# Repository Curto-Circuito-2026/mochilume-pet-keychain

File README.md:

# 🎮 Mochilume: Portable Wireless Battle Console & OS

O **Mochilume** é um console portátil de bolso open-hardware projetado para trazer de volta a nostalgia dos bichinhos virtuais (estilo Tamagotchi), combinando mecânicas de exploração do mundo real (estilo Pokémon GO) com batalhas multijogador locais e conectividade em nuvem. 

O ecossistema opera em uma arquitetura híbrida de rede: o progresso do jogador e os status do pet são sincronizados na nuvem via **Wi-Fi**, enquanto as batalhas de proximidade entre consoles ocorrem de forma descentralizada via rádio **LoRa**.

---

## 📸 Galeria do Projeto

### Hardware & Placas (Fabricação Caseira)
<table>
  <tr>
    <td align="center"><strong>Placa do Console</strong></td>
    <td align="center"><strong>Placa de Energia</strong></td>
  </tr>
  <tr>
    <td></td>
    <td></td>
  </tr>
</table>

---

### Interface do Usuário & Gameplay (Tela 240x240)
<table>
  <tr>
    <td align="center"><strong>Menu Principal</strong></td>
    <td align="center"><strong>Tela de Batalha (LoRa PvP)</strong></td>
    <td align="center"><strong>Tela do Mochilume (Status)</strong></td>
  </tr>
  <tr>
    <td valign="top"></td>
    <td valign="top"></td>
    <td valign="top"></td>
  </tr>
</table>

---

---
## 🕹️ Dinâmica do Jogo & Gameplay

* **Tamagotchi + Pokémon GO:** O jogador cuida, alimenta e treina o seu "Mochilume". A evolução e os atributos do pet estão diretamente atrelados à movimentação do jogador no mundo real.
* **Mova-se para Evoluir:** Utilizando os sensores de movimento integrados, o console rastreia os passos do jogador. **Quanto mais você anda na vida real, mais forte o seu pet fica**, ganhando experiência, atributos e subindo de nível.
* **Batalhas Locais via LoRa:** Encontrou um colega que também tem um Mochilume? Os consoles se conectam ponto a ponto (P2P) via rádio de longo alcance para batalhas em tempo real, sem depender de internet, roteadores ou redes móveis.

---

## 🛠️ Engenharia de Hardware & Fabricação

O hardware foi inteiramente projetado, roteado e fabricado de forma artesanal, utilizando processos avançados de prototipagem rápida:

* **Fabricação da PCB:** As placas de circuito impresso (PCBs) foram confeccionadas manualmente utilizando o método de **termotransferência e corrosão química**, com layout em **Dual Layer (Dupla Face)** para otimização de espaço e plano de terra.
* **Módulo de Energia Independente:** Equipado com um sistema de gerenciamento de carga para **célula de lítio recarregável** integrado à placa, permitindo o uso totalmente portátil do console.
* **Interface Visual:** Display circular colorido de **240x240 pixels** (Driver GC9A01A), operando com taxa de atualização acelerada via barramento SPI de alta frequência.

---

## 🧠 Arquitetura de Firmware (Sistemas Embarcados)

O software do console foi desenvolvido em **C++** sobre o framework **PlatformIO**, focado em gerenciamento eficiente de recursos de rádio e energia:

* **Gerenciamento de Rede Híbrido:**
  * **Conectividade Wi-Fi:** Utilizada estritamente para autenticação do jogador e comunicação HTTP assíncrona com a API externa para salvar o estado do jogo.
  * **Comunicação LoRa (LLCC68):** Dedicada exclusivamente ao protocolo de rede sem fio de baixa latência para transmissão dos pacotes de dados das batalhas PvP (Player vs Player).
* **Filtro de Bateria Não-Bloqueante:** Monitoramento do divisor de tensão da bateria filtrado com **Média Móvel (100 amostras consecutivas)** e controlado por temporização com **`millis()`** encapsulado de forma estática. A leitura roda estritamente a cada 5 segundos para garantir que picos de consumo do Wi-Fi/LoRa não gerem *falsos positivos* de bateria fraca ou travem as requisições de rede.
* **Pedômetro via Hardware:** Algoritmo baseado em máquina de estados para validação de passos reais através da magnitude de aceleração tridimensional da IMU (MPU6050), armazenando os dados em buffers (*batches*) para sincronização otimizada.

---

## 🌐 Nuvem e Infraestrutura (Backend)

O Mochilume não perde o progresso caso seja desligado. Os dados persistentes são salvos globalmente através de uma infraestrutura escalável:

* **Mochilume API:** Desenvolvida em **C# (.NET Web API)** e hospedada na nuvem da **Azure**. Ela atua como um Gateway de serviços que recebe chamadas HTTP puras originadas do Wi-Fi do console. A API processa a lógica de evolução dos pets, validação de dados e pontuação global.
* **Persistência de Dados:** Banco de dados relacional **PostgreSQL** hospedado de forma isolada no **Supabase**. O esquema de tabelas (jogadores, inventário, histórico e status dos pets) é versionado e gerenciado por **Migrations** via Entity Framework Core (EF Core) a partir do projeto C#.

---

## 🚀 Como Compilar e Rodar

### Backend (API)
1. Navegue até a pasta da API em C#.
2. Configure a string de conexão do Supabase/Postgres no seu `appsettings.json`.
3. Execute as migrations e suba o servidor:
   ```bash
   dotnet ef database update
   dotnet run

### Firmware (Console)

> ⚠️ **ATENÇÃO CRÍTICA DE HARDWARE (eFuses do ESP32):**
> Como o design da PCB em Dual Layer otimizou ao máximo as trilhas manuais por corrosão, alguns pinos de boot/strapping (como o GPIO 12 / MTDI) foram utilizados para os barramentos de periféricos. 
> Antes de realizar o upload do firmware, é **obrigatório** configurar/queimar os eFuses de tensão interna do regulador flash do ESP32 para travar em 3.3V nativo e ignorar o estado do pino no boot. Caso contrário, a placa entrará em loop de *boot fail*.
>
> Para queimar o eFuse via terminal (ferramenta `esptool.py` do Espressif):
> ```bash
> espefuse.py --port COM_DO_SEU_CONSOLE set_flash_voltage 3.3V
> ```
> *Nota: Este processo é irreversível e configura o chip especificamente para o layout desta PCB.*

1. Abra a pasta `mochilume-code` no VS Code com a extensão **PlatformIO** ativa.
2. Abra o arquivo `include/HalConfig.h` (ou onde estiverem as suas constantes de hardware) e atualize a variável da URL da API com o endereço de produção gerado pela sua Azure Free Tier:
   ```cpp
   const char* API_URL = "[https://seu-app-service.azurewebsites.net/api/v1/pet](https://seu-app-service.azurewebsites.net/api/v1/pet)";

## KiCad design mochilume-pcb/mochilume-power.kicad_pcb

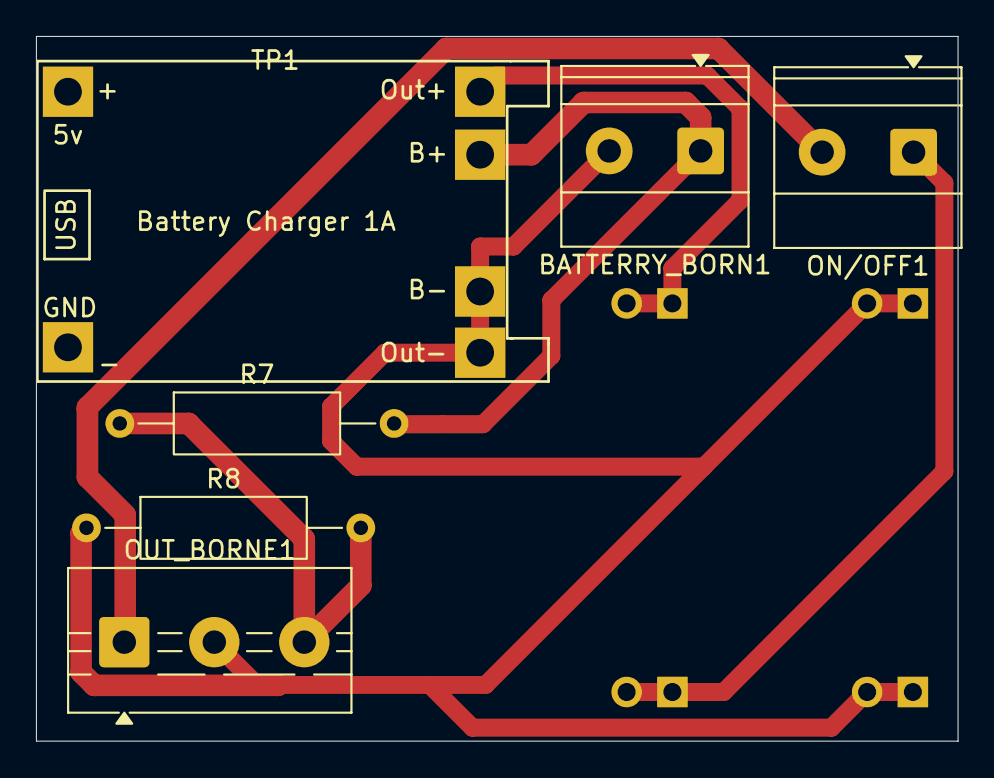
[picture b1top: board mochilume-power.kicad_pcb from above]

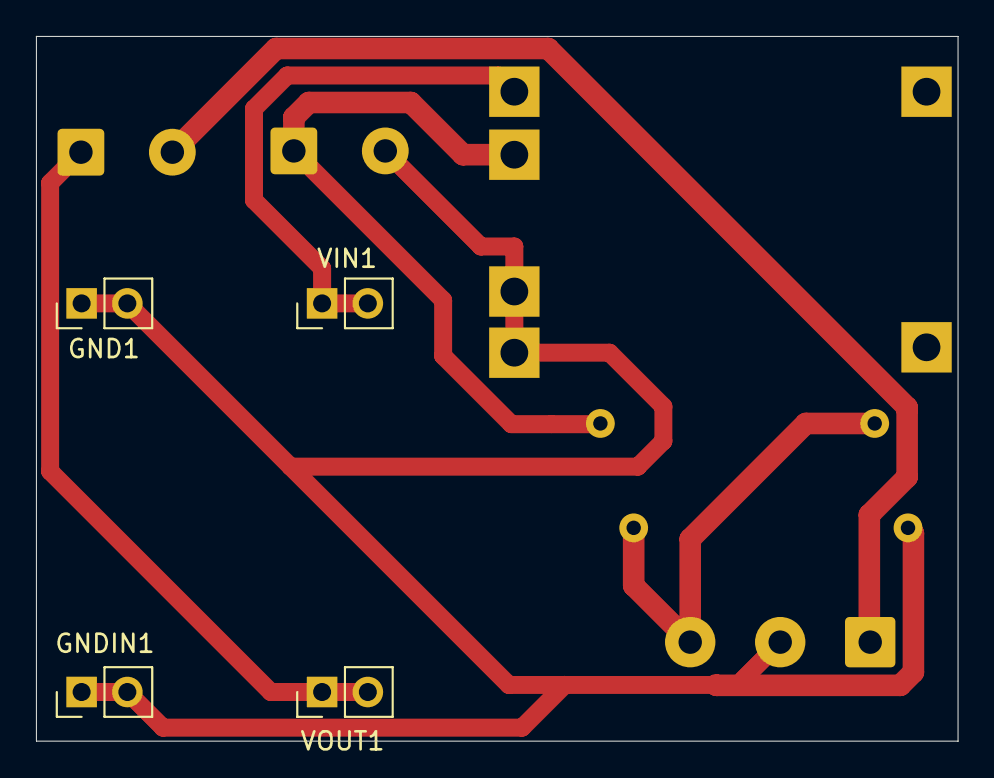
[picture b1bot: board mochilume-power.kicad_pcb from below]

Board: 2 copper layers, 51.2 x 39.2 mm, 10 parts (4 on the bottom side), 6 nets.

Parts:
BATTERRY_BORN1: TerminalBlock_Phoenix_MKDS-1,5-2-5.08_1x02_P5.08mm_Horizont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
GND1: PinHeader_1x02_P2.54mm_Vertical
GNDIN1: PinHeader_1x02_P2.54mm_Vertical
ON/OFF1: TerminalBlock_Phoenix_MKDS-1,5-2-5.08_1x02_P5.08mm_Horizont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
OUT_BORNE1: Screw_Terminal_01x03; TerminalBlock_MaiXu_MX126-5.0-03P_1x03_P5.00mm
R7, R8: 10K; R_Axial_DIN0309_L9.0mm_D3.2mm_P15.24mm_Horizontal
TP1: TP4056-18650
VIN1: PinHeader_1x02_P2.54mm_Vertical
VOUT1: PinHeader_1x02_P2.54mm_Vertical

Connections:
BATERIA: OUT_BORNE1.3, R7.1, R8.2
BATTERY +: BATTERRY_BORN1.1, R7.2, TP1.5 (B+)
GND: BATTERRY_BORN1.2, GND1.1, GND1.2, GNDIN1.1, GNDIN1.2, OUT_BORNE1.2, R8.1, TP1.4 (GNDOUT), TP1.6 (B-)
VCC: ON/OFF1.2, OUT_BORNE1.1
VCC_IN: ON/OFF1.1, VOUT1.1, VOUT1.2
VIN: TP1.3 (VOUT), VIN1.1, VIN1.2

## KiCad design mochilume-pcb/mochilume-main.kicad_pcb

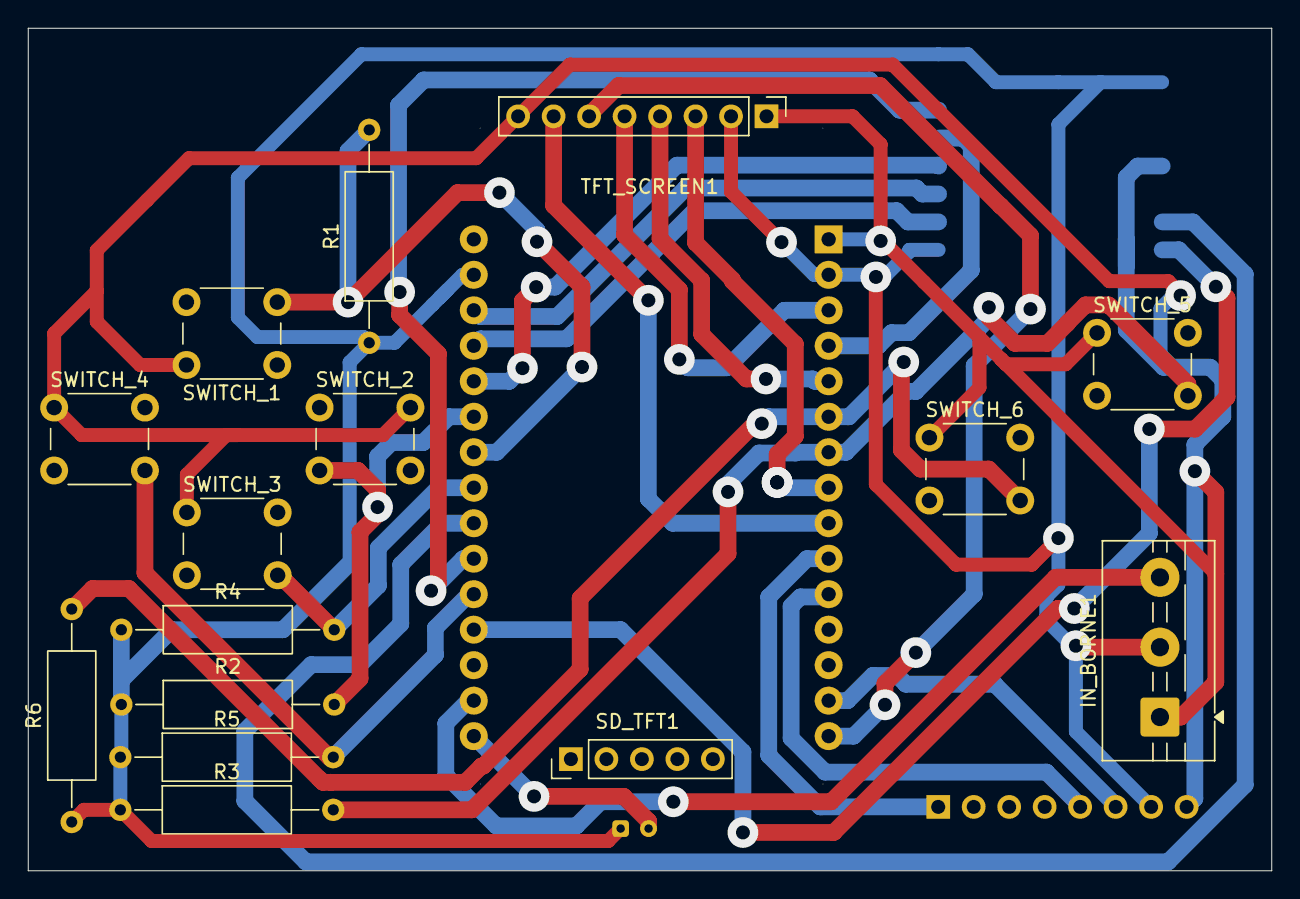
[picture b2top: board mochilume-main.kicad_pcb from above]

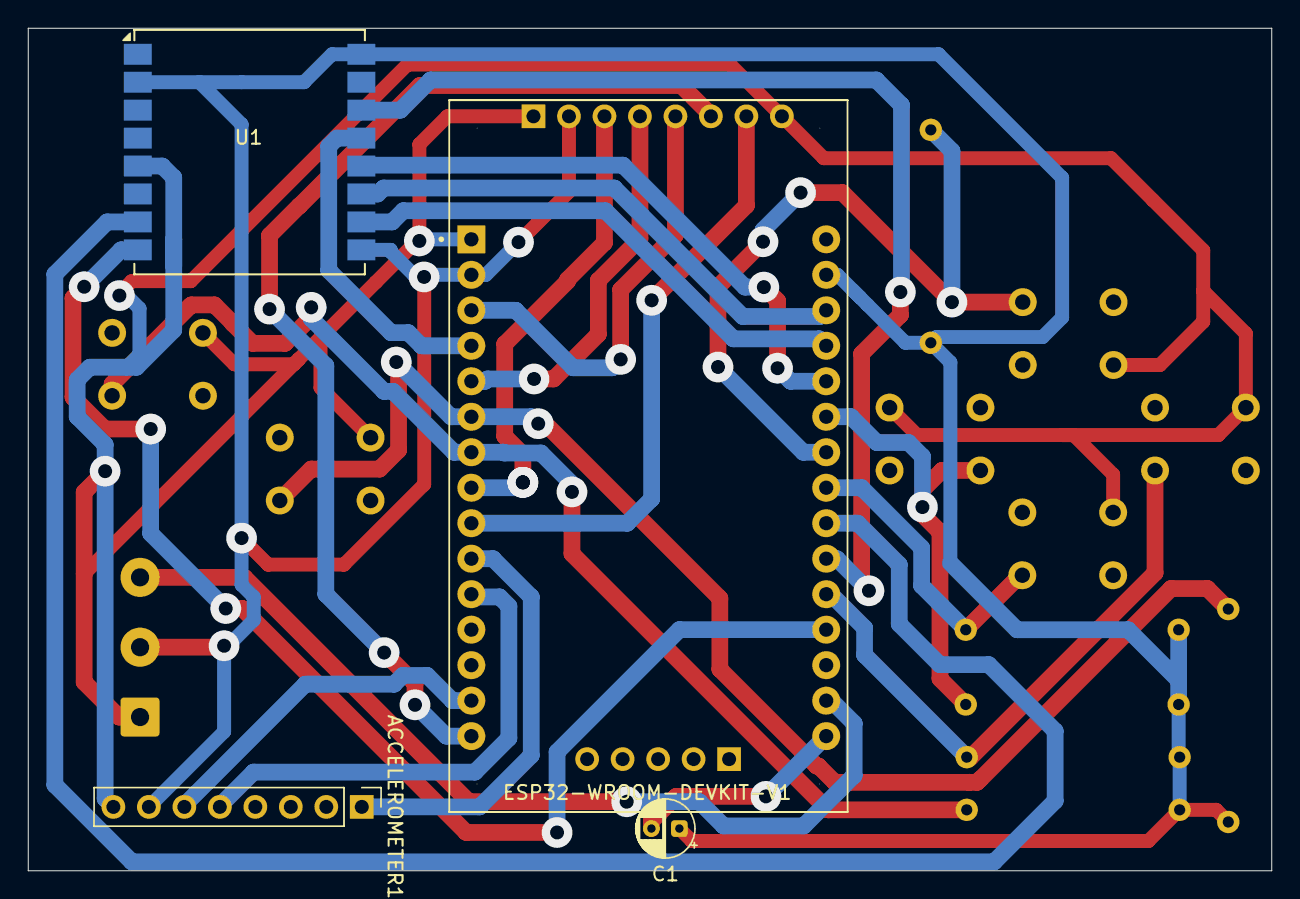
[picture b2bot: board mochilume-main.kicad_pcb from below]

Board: 2 copper layers, 89.0 x 60.3 mm, 19 parts (4 on the bottom side), 25 nets.

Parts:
ACCELEROMETER1: PinHeader_1x08_P2.54mm_Vertical
C1: 10uF; CP_Radial_D4.0mm_P2.00mm
ESP32-WROOM-DEVKIT-V1: MODULE_ESP32_DEVKIT_V1
IN_BORNE1: Screw_Terminal_01x03; TerminalBlock_MaiXu_MX126-5.0-03P_1x03_P5.00mm
R1, R2, R3, R4, R5, R6: 10K; R_Axial_DIN0309_L9.0mm_D3.2mm_P15.24mm_Horizontal
SD_TFT1: PinHeader_1x05_P2.54mm_Vertical
SWITCH_1, SWITCH_2, SWITCH_3, SWITCH_4, SWITCH_5, SWITCH_6: SW_PUSH_6mm
TFT_SCREEN1: PinHeader_1x08_P2.54mm_Vertical
U1: llcc68_custom_module; Ai-Thinker-Ra-01-LoRa

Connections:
AC_SCL: ACCELEROMETER1.6, ESP32-WROOM-DEVKIT-V1.14 (D22)
AC_SDA: ACCELEROMETER1.5, ESP32-WROOM-DEVKIT-V1.11 (D21)
AC_TRIG: ACCELEROMETER1.1, ESP32-WROOM-DEVKIT-V1.10 (D19)
BATERIA: ESP32-WROOM-DEVKIT-V1.17 (VP), IN_BORNE1.3
GND: ACCELEROMETER1.7, C1.1, ESP32-WROOM-DEVKIT-V1.2 (GND), ESP32-WROOM-DEVKIT-V1.29 (GND), IN_BORNE1.2, R1.1, R2.1, R3.1, R4.1, R5.1, R6.1, TFT_SCREEN1.2, U1.2 (GND), U1.9 (GND), U1.16 (GND)
LORA_BUSY: ESP32-WROOM-DEVKIT-V1.19 (D34), U1.8 (BUSY)
LORA_CS: ESP32-WROOM-DEVKIT-V1.4 (D2), U1.13 (~NSS)
LORA_DIO1: ESP32-WROOM-DEVKIT-V1.22 (D33), U1.7 (DIO1)
LORA_MISO: ESP32-WROOM-DEVKIT-V1.27 (D12), U1.10 (MISO)
LORA_MOSI: ESP32-WROOM-DEVKIT-V1.28 (D13), U1.11 (MOSI)
LORA_RST: ESP32-WROOM-DEVKIT-V1.21 (D32), U1.14 (~RESET)
LORA_SCK: ESP32-WROOM-DEVKIT-V1.26 (D14), U1.12 (SCK)
unnamed: C1.2, ESP32-WROOM-DEVKIT-V1.16 (EN)
SW_1: ESP32-WROOM-DEVKIT-V1.24 (D26), R1.2, SWITCH_1.2
SW_2: ESP32-WROOM-DEVKIT-V1.25 (D27), R2.2, SWITCH_2.2
SW_3: ESP32-WROOM-DEVKIT-V1.23 (D25), R4.2, SWITCH_3.2
SW_4: ESP32-WROOM-DEVKIT-V1.20 (D35), R5.2, SWITCH_4.2
SW_5: ESP32-WROOM-DEVKIT-V1.7 (TX2), R3.2, SWITCH_5.2
SW_6: ESP32-WROOM-DEVKIT-V1.6 (RX2), R6.2, SWITCH_6.2
TFT_A0: ESP32-WROOM-DEVKIT-V1.3 (D15), TFT_SCREEN1.5
TFT_CS: ESP32-WROOM-DEVKIT-V1.8 (D5), TFT_SCREEN1.3
TFT_RES: ESP32-WROOM-DEVKIT-V1.5 (D4), TFT_SCREEN1.4
TFT_SCK: ESP32-WROOM-DEVKIT-V1.9 (D18), TFT_SCREEN1.7
TFT_SDA: ESP32-WROOM-DEVKIT-V1.15 (D23), TFT_SCREEN1.6
VCC: ACCELEROMETER1.8, ESP32-WROOM-DEVKIT-V1.1 (3V3), IN_BORNE1.1, SWITCH_1.1, SWITCH_2.1, SWITCH_3.1, SWITCH_4.1, SWITCH_5.1, SWITCH_6.1, TFT_SCREEN1.1, TFT_SCREEN1.8, U1.5 (VDD)

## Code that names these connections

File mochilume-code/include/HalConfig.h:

#ifndef HAL_CONFIG_H
#define HAL_CONFIG_H

#include <Arduino.h>

// --- DISPLAY SETTINGS (GC9A01) ---
#define TFT_RES      4
#define TFT_CS       5
#define TFT_DC       15
#define TFT_MOSI     23
#define TFT_SCLK     18
#define TFT_BL       22

#define SCREEN_WIDTH  240
#define SCREEN_HEIGHT 240
#define SCREEN_RADIUS 120
#define SCREEN_CENTER 120

// --- BUTTONS ---
//definir pinos reais
#define BTN_UP      26    
#define BTN_DOWN    25    
#define BTN_LEFT    35    
#define BTN_RIGHT   27    
#define BTN_A       16   
#define BTN_B       17     

// --- SYSTEM SETTINGS ---
#define TARGET_FPS   60
#define FRAME_DELAY  (1000 / TARGET_FPS)

// --- LORA SX1268 (SPI) ---

#define LORA_SPI_SCK  14  
#define LORA_SPI_MOSI 13  
#define LORA_SPI_MISO 12  

#define LORA_CS        2  
#define LORA_RST      32  
#define LORA_DIO1     33  
#define LORA_BUSY     34  

//Battery
#define BATTERY_PIN 36

// --- STORAGE (SD CARD) ---
#define SD_CS        2

// --- SENSORS (I2C) ---
#define MPU_SDA      21
#define MPU_SCL      22
#define MPU_TRIG     19
// --- API URLS ---
#define API_BASE_URL "https://api-mochilume-acd9htg9ghhacghy.brazilsouth-01.azurewebsites.net"
// Global
#define HEALTH_ENDPOINT       API_BASE_URL "/health"
// Auth
#define AUTH_REGISTER_ENDPOINT API_BASE_URL "/api/Auth/register"
#define AUTH_LOGIN_ENDPOINT    API_BASE_URL "/api/Auth/login"
// Save System
#define SAVE_UPLOAD_ENDPOINT   API_BASE_URL "/api/Save/upload"
// Para o download, você pode concatenar o username direto na string se preferir, 
// ou usar como base para um sprintf/snprintf formatado:
#define SAVE_DOWNLOAD_BASE_URL API_BASE_URL "/api/Save/"
#define SAVE_DOWNLOAD_SUFFIX   "/download"

//PATH DE ARQUIVO DE SAVE
#define PLAYER_SAVE_PATH "/player.sav"


#endif

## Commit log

2026-03-18 docs: add prd
2026-03-18 docs: create PRD.md
2026-03-18 docs: add prd.md
2026-03-18 docs: prd
2026-03-18 Revert "docs: add prd.md"
    This reverts commit 1c1278380b18008ab08b6e6106bdf214605d4a9f.
2026-03-27 add agent context
2026-03-27 FEAT: initial graphic framework base
2026-03-28 FEAT: initial activity framework
2026-03-29 refactor: instantiate tft in Activity base class
2026-03-30 chore: rename Doc folder to docs
2026-03-30 feat: add mpu6050 libs
2026-03-30 feat: add input manager base
2026-04-15 feat: create initial player save struct
2026-04-15 feat: change board filesystem to littleFS
2026-04-15 feat: add save manager
2026-04-15 feat: add save file path to halconfig
2026-04-21 fix: solve the mcu restarting issue caused by input manager not correctly initiated
2026-04-21 feat: change input manager to update all IO devices
2026-04-21 docs: update wrong info in comment
2026-04-21 feat: implement hierarchical UI system with menu navigation
2026-05-01 update pcb: remove sd card tracks
2026-05-01 fix: set switch buttons to pull down and change pins
2026-05-01 feat: add radioLib to platformio.ini requirements
2026-05-01 fix: change pins to connect lora module to HSPI and tft screen to VSPI
2026-05-01 feat: add battery readable pin
2026-05-01 FEAT: UI Framework (screen management, uielements) + DOUBLE buffer (stripped rendering)
2026-05-02 feat pcb: add lora module and 2 buttons to kicad schematic
2026-05-03 FEAT: Navigation
2026-05-03 fix pcb: fix schematics bugs
2026-05-04 feat pcb: add custom footprint lib to lora module
2026-05-04 fix pcb: fix custom lib wrong pins
2026-05-04 fix pcb: update footprints and add pcb sketch without vias
2026-05-06 refactor pcb: split power and logic into 2 pcbs
2026-05-06 feat pcb: add via tracking to power pcb
2026-05-06 fix power pcb: fix out bornier footprint
2026-05-06 feat pcb: add esp32 schematic symbol and footprint
2026-05-06 feat main pcb: add vias tracking to main pcb
2026-05-16 docs pcb: add todo to fix pcb design problems later
2026-05-16 Update TODO.md with PCB design issues and fixes
2026-05-20 fix: define real buttons pin to halconfig
2026-05-20 fix: unconnected via between tft_cs and esp 32 pin 8
2026-05-20 fix power pcb: remove diode that disable tpu4056
2026-05-20 docs: update pcb todo
2026-05-22 FEAT: screen capture input queue
2026-05-22 FEAT: initial Apps
2026-05-25 FEAT: Mochilume pet data flow; user.json config; mochilume stats screen
2026-05-25 FEAT: WifiManager
2026-05-26 FIX: Build Fixes
2026-05-30 fix compilations errors
2026-05-30 update .gitignore to add api variables
2026-05-30 feat api: adjust models and create DTOs
2026-05-30 feat api: add database setup and migrations without sensitive string
2026-05-30 feat api: add hybrid generic repositories for models
2026-05-30 feat api: add auth logic and controllers
2026-05-30 feat api: add upload and download save
2026-05-30 feat api: configure DI and swagger
2026-05-30 chore api: initial boilerplate setup
2026-06-04 feat api: add health check endpoint
2026-06-04 Add or update the Azure App Service build and deployment workflow config
2026-06-04 Refactor GitHub Actions workflow for Azure deployment
2026-06-04 chore api: enable swagger in all environments
2026-06-04 feat api: add exception middleware to log unhandled errors
2026-06-04 fix api: enable retry on failure for transient database errors
2026-06-05 remove line that flood serial
2026-06-05 feat: add api endpoints to hal config
2026-06-05 feat: add api dtos
2026-06-05 fix: update wifi manager to async make http requests
2026-06-05 fix: update wifi manager to async make http requests .h
2026-06-05 feat: add callables to integrate with api
2026-06-05 api integration test
2026-06-05 feat: mochilume pages + uiInput
2026-06-06 feat: config pages + uiKeyboard
2026-06-07 fix: legacy cleanup
2026-06-07 fix: file read/write cycle
2026-06-07 fix: pet skill change
2026-06-07 fix: fix lora module pines in halconfig
2026-06-07 feat: add radiolib to lora manager implementation
2026-06-07 feat: lora manager initial implementation
2026-06-07 feat: lora battle first pass
2026-06-07 FIX: Package Type
2026-06-07 FIX: Show while not in battle
2026-06-07 fix: battle ui
2026-06-07 feat: battle turns
2026-06-07 fix: oponent pet info
2026-06-08 fix: send skill
2026-06-08 fix: logs
2026-06-08 fix: bugfix
2026-06-08 fix: more logs
2026-06-08 fix: retransmition to solve battle turn
2026-06-08 fix: package size
2026-06-08 fix: delay salva vidas
2026-06-08 fix: refresh turn
2026-06-08 fix: battle screen text
2026-06-08 feat: handhsake
2026-06-08 feat: keep-alive + win condition
2026-06-08 feat: deviceID
2026-06-08 feat: full battle cycle
2026-06-08 feat: pet skills impact damage calculation
2026-06-08 feat: icons + skill descriptions
2026-06-09 feat: add baterry pin to future battery level
2026-06-09 feat: add baterry level and MPU6050 steps update
2026-06-09 fix: remove get steps println
2026-06-09 fix: battery level function redefinition
2026-06-09 refactor api: merge login and register to increase simplicity to cpp requests
2026-06-09 feat: steps and battery icon
2026-06-09 feat: config login
2026-06-09 feat: read battery level by avg
2026-06-09 feat: change compiler to release mode and disable OTA to decrease flash usage
2026-06-09 feat: add login and sign out to config screen
2026-06-09 feat: add steps save into file
2026-06-09 fix: wifi list slow down config open
2026-06-09 feat: upload save to cloud
2026-06-09 feat: download from cloud
2026-06-09 refactor(api): download save get only one pet looking to bigger id
2026-06-09 fix: pet null pointer when give xp
